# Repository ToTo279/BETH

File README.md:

# BETH - Badminton Equipment for Training and Health

## Projektbeschreibung
Das Elektronikprojekt konzentriert sich auf verschiedene Aspekte der Elektrotechnik, darunter die Programmierung von Mikrocontrollern, die Analyse und Umsetzung der Energieversorgung kleinerer Geräte sowie die Implementierung von Sensoren, optischen und akustischen Bausteinen. Das Hauptziel besteht darin, ein System zu entwickeln, das sowohl im sportlichen Bereich als auch im Freizeitbereich Anwendung findet. BETH (Badminton Equipment for Training and Health) wurde entwickelt, um Spielern die Möglichkeit zu geben, ihre Reaktionsfähigkeit, Bewegungskoordination und Ausdauer zu verbessern, indem es eine dynamische und unterhaltsame Umgebung schafft.

## Funktionen und Technologien
- Programmierung von ESP32 Mikrocontrollern und eines Raspberry Pi's
- Analyse des Energiekonsums und Umsetzung der Energieversorgung kleinerer Geräte
- Integration von Sensoren, Licht- und Tonbausteinen für innovative und interaktive Systeme

---

### Gehäuse
Das BETH-System besteht aus einer Basisstation und vier Satelliten. Die Basisstation, bestehend aus einem Raspberry Pi und einem Touchdisplay, verwendet ein käuflich erhältliches Gehäuse für optimale Bedienung und Sichtbarkeit.

Für die Satelliten wurde ein Gehäuse mittels 3D-Druck und CAD-Programm entworfen. Tough PLA für Unterteil und Brücke sowie CPE+ für Oberteil und Status-LED-Fenster sorgen für Robustheit und Flexibilität.

Das Unterteil des Gehäuses verfügt über Öffnungen für Lautsprecher, Taster, USB-C-Buchse und Status-LED. Auflageflächen für Spannungsversorgungs- und LED-Platinen sind integriert. M3-Schmelzgewinde gewährleisten eine sichere Schraubverbindung.

Die Brücke zwischen den Platinen ermöglicht eine modulare Montage. Das Oberteil beinhaltet einen LED-Streifen, einen Touchsensor und drei Abstandssensoren. Die glatte Oberfläche gewährleistet eine angenehme Haptik.

**Modelle für Gehäuse und Platinen befinden sich im Ordner "Modelle".**

### Energieversorgung

Dieser Abschnitt bietet einen Überblick über das Energiemodul des BETH-Projekts, einschließlich seiner Integration, Funktionsweise, verwendeten Komponenten, Schaltplan und Leiterplatte, sowie Tests und Reflexionen.

#### Eingliederung in das Projekt

Die Entscheidung für die Energieversorgung der Satelliten basierte auf der Wahl zwischen Netzbetrieb, Batterie oder Akkubetrieb. Die Akkubetriebsoption wurde gewählt, um Flexibilität, einfache Handhabung und ästhetisches Design zu gewährleisten. Das Energiemodul ist ein Schlüsselelement der Satelliten, neben dem ESP32 Mikrocontroller.

#### Funktionsweise

Das Energiemodul erfüllt verschiedene Anforderungen, darunter eine 45- bis 60-minütige Energieversorgung, Aufladung über einen USB-C-Anschluss, Bereitstellung von 5 Volt DC bei maximal 1,5 Ampere, Ein- und Ausschalten am Gehäuse, softwaregesteuertes Ausschalten und Schutz vor Gefahren.

#### Verwendete Baugruppen

- Batteriezelle (XTAR 18650)
- Charge IC (BQ24092DGQR)
- Step-up DC-DC Converter (TPS61085)
- eFuse (TPS259621DDAT)
- Ein-Aus-Schalter (CMOS J-K Flip Flop)
- Protection IC (XB8089D)

#### Schaltplan und Leiterplatte

Der Schaltplan und die Leiterplatte wurden unter Berücksichtigung der Datenblätter der Komponenten entwickelt. Der Schaltplan enthält ICs, passiven Bauteilen und Testpunkten. Die Leiterplatte wurde sorgfältig gestaltet, wobei auf großräumige Flächen an energiereichen Stellen und Testpunkte für einfaches Debugging geachtet wurde.

### Audio
#### Eingliederung in das Projekt
Die Umsetzung einer effektiven Audiowiedergabe erfordert präzise Signalverarbeitung und Kontrolle. Im Fokus steht die Audiowiedergabe, bei der mehrere Schaltungselemente kombiniert wurden, um optimale Klangqualität und Steuerbarkeit zu gewährleisten. Die Grundlage bildet ein Audioplayer-Modul, dem im Verlauf der Realisierung verschiedene Elemente hinzugefügt wurden.

##### Funktionsweise
1. **DF Player**
   - Ein DF Player bzw. ein Audioplayer-Modul von DFRobot wird verwendet.
   - Speziell für die Wiedergabe von Audiodateien mit einem einfachen Steuerungsprotokoll konzipiert.
   - Unterstützt Funktionen wie Abspielen, Pausieren, Stoppen, Vor- und Zurückspulen von Audiotracks.
   - Über eine serielle Schnittstelle (UART) vom Mikrocontroller (ESP32S) gesteuert.

2. **Addierer und Rekonstruktionsfilter**
   - Verwendung einer Schaltung mit einem Operationsverstärker (OPV), um rechte und linke Stereosignale zu kombinieren.
   - Ein Rekonstruktions-Tiefpassfilter minimiert Aliasing-Effekte und glättet das digitale Signal.

3. **Audio Verstärker**
   - Der LM386 Audioverstärkerchip ermöglicht eine effektive Verstärkung von Audiosignalen.
   - Die Schaltung umfasst verschiedene Bauteile, die in ihrer Kombination eine qualitativ hochwertige Audiowiedergabe gewährleisten.

4. **DC/DC Wandler**
   - Ein DC/DC-Wandler wird eingesetzt, um die Batteriespannung von +5V auf +12V umzuwandeln.
   - Ein Filterkondensator minimiert Eingangs- und Ausgangswelligkeit.
   - Eine Elektromagnetische Verträglichkeit (EMC) Schaltung gewährleistet störungsfreies Arbeiten in elektromagnetisch sensiblen Umgebungen.

##### Anleitung zur Nutzung
1. Lade Audiofiles auf die micro SD-Karte.
2. Verbinde die serielle Schnittstelle des DF Players mit der Steuerungseinheit.
3. Steuere die Audiowiedergabe über UART-Befehle.

##### Hinweise
- Beachte die Platzbeschränkungen bei der Implementierung der Audiofunktionen.
- Stelle sicher, dass die Spannungsversorgung und EMC-Richtlinien eingehalten werden.

### LED-Beleuchtung
#### Eingliederung in das Projekt
Die Integration der LED-Beleuchtung in das Projekt bietet eine ästhetische Komponente und erweitert die Funktionalität. Die Wahl der RGB-LEDs WS2812B ermöglicht die flexible Ansteuerung jeder einzelnen LED, was eine vielfältige Gestaltung der Beleuchtung und die Umsetzung verschiedener Spielmodi ermöglicht. Die LEDs dienen auch zur Anzeige von Statusinformationen wie dem Verbindungsstatus und dem Batteriezustand.

#### Funktionsweise
Die Platine für die LED-Beleuchtung wurde so gestaltet, dass sie neben den RGB-LEDs WS2812B auch alle notwendigen Komponenten enthält, um eine nahtlose Integration in das Gesamtsystem zu gewährleisten. Die Anordnung der LEDs in einem Ring und dem LED-Streifen ermöglichen die Erzeugung kreativer Lichteffekte, die das Spielerlebnis intensivieren.

Die WS2812B RGB-LEDs haben vier Pins: Versorgungsspannung, Masse, Eingangssignal und Ausgangssignal. Die Verbindung zwischen den LEDs erfolgt durch Verknüpfung des Ausgangssignal-Pins einer LED mit dem Eingangssignal-Pin der nächsten LED. Die Status-LED auf der Seite des Gehäuses kommuniziert über verschiedene Farben und Blinkmuster wichtige Informationen, wie den Verbindungsstatus mit anderen Satelliten oder den Batteriezustand.

#### Schaltplan
Es wurden 16 LEDs auf einer eigenen Platine kreisförmig angeordnet. Die LEDs sind mit dem Mikrocontroller verbunden, um das Eingangssignal, die Spannungsversorgung und die Masse zu erhalten, und leiten das Signal an die Status-LED und den LED-Streifen weiter.

#### PCB
Die Leiterplatte (PCB) wurde entsprechend dem Schaltplan erstellt. Die LEDs wurden in einem Kreis angeordnet, und auf der anderen Seite der Platine wurden der große Kondensator und der Widerstand platziert.

#### Programmierung
Für die Steuerung der LEDs wurde die Neopixel-Bibliothek von Adafruit Industries verwendet. Die Programmierung ermöglicht eine flexible und anpassbare visuelle Gestaltung, um das LEDmintons-Erlebnis zu verbessern. Die Integration dieser Programmierfunktionalitäten erlaubt die Steuerung der Beleuchtungseffekte in Echtzeit während des Spielbetriebs.

### Sensorik
#### Eingliederung in das Projekt
Im Sensorik-Kapitel wird die Integration der im Projekt verwendeten Sensoren beschrieben. Sensoren sind in der Lage, Informationen von der Umgebung aufzunehmen und elektrische Signale zu erzeugen. Im Projekt wurden Sensoren ausgewählt, die spezifische Anforderungen erfüllen sollten, darunter die Detektion des Badmintonschlägers auf unterschiedlichen Distanzen und die schnelle Reaktion auf Bewegungen.

#### Anforderungen
Die Auswahl der Sensoren erfolgte unter Berücksichtigung von Anforderungen wie der Reaktionsgeschwindigkeit und der Fähigkeit, Bewegungen auf kurze und lange Distanzen zu detektieren. Es wurden TOF-Sensoren (Time of Flight) ausgewählt, um die Entfernungen zuverlässig zu messen, sowie der eingebaute Touchsensor des ESP32 für die Detektion von Berührungen.

#### Funktionsweise
**TOF Sensoren**
Die Entfernungsmessung wird von TOF-Sensoren übernommen. Diese Sensoren wurden aufgrund ihrer Zuverlässigkeit, schnellen Reaktion und geringen Größe ausgewählt. Sie sind in der Lage, Entfernungen von 40 mm bis 4 m mit einer Genauigkeit von ±5 % zu messen. Die Messung basiert auf der Laufzeitmessung von Licht, das zum Zielobjekt geschossen wird und reflektiert zurückkehrt.

**Touch Sensor**
Der Touchsensor basiert auf den Touchpins des ESP32. Die Berührung einer Metallplatte, die mit einem Pin verbunden ist, sendet ein elektrisches Signal an den ESP32. Schutzmaßnahmen, wie eine Supressordiode und ein Widerstand, wurden implementiert, um Überladungen zu verhindern.

**Programmierung und Interrupts**
Um eine schnelle Reaktion der TOF-Sensoren zu gewährleisten, wurden Interrupts in der Programmierung verwendet. Diese ermöglichen eine zuverlässige Detektion von Umweltveränderungen und eine unmittelbare Weiterleitung an den ESP32.

### Kommunikation
#### Eingliederung in das Projekt
Dieser Abschnitt beschäftigt sich mit der technischen Implementierung und Realisierung der Kommunikation zwischen den Satelliten (ESP32) und der Basisstation (Raspberry Pi). Die Kommunikation spielt eine entscheidende Rolle, da sämtliche Benutzerinteraktionen über die Basisstation erfolgen.

#### Kommunikationsmethoden
Zur Gestaltung des Projekts wurden zwei Kommunikationsmethoden in Betracht gezogen: Bluetooth und drahtlose Verbindung (WLAN). Nach sorgfältiger Überlegung wurde WLAN als die bessere Option gewählt, da es die spezifizierten Anforderungen besser erfüllt. Als Kommunikationsprotokoll wurde TCP (Transmission Control Protocol) ausgewählt, um eine stabile und zuverlässige Verbindung zu ermöglichen.

#### Anforderungen
Die formulierten Anforderungen umfassen unter anderem die gleichzeitige Verbindung aller Satelliten mit der Basisstation, eine stabile Verbindung, schnelle Erkennung von Unterbrechungen, minimaler Paketverlust, automatische Wiederherstellung der Verbindung nach Unterbrechungen und unabhängige Verbindungen zwischen der Basisstation und den Satelliten.

#### Implementierung
Die Kommunikation erfolgt über WLAN unter Verwendung von TCP. Die Basisstation (Raspberry Pi) erstellt einen drahtlosen Hotspot, und die Satelliten (ESP32) stellen eine TCP-Verbindung her. Die Kommunikation erfolgt in JSON-Format für die Übertragung von Nachrichten.

##### Raspberry Pi Programmierung
Die Basisstations-Software wurde in Python (Version 3.12) implementiert. Sie erstellt einen kabellosen Hotspot, verwaltet die Kommunikation und bietet eine grafische Benutzeroberfläche (GUI) für Benutzerinteraktionen.

##### ESP-32 Programmierung
Die Satelliten-Software wurde in C++ mit Hilfe von Espressifs Wifi-Bibliothek und ArduinoJson implementiert. Die Satelliten senden regelmäßig Nachrichten, die die Satellite-ID und den Batteriestand enthalten.

##### Test der Kommunikation
Verschiedene Testfälle wurden durchgeführt, darunter der reibungslose Betrieb paralleler Verbindungen und die erfolgreiche Erkennung von Verbindungsunterbrechungen. Die Kommunikation wurde über mehrere Stunden ohne Unterbrechungen getestet.

---

## Installation und Nutzung
1. Klone das Repository: `git@github.com:ToTo279/BETH.git`
2. Folge den Anweisungen in der Installationsanleitung, um das System einzurichten.
3. Erkunde die verschiedenen Funktionen und Anwendungsbereiche im Projekt.

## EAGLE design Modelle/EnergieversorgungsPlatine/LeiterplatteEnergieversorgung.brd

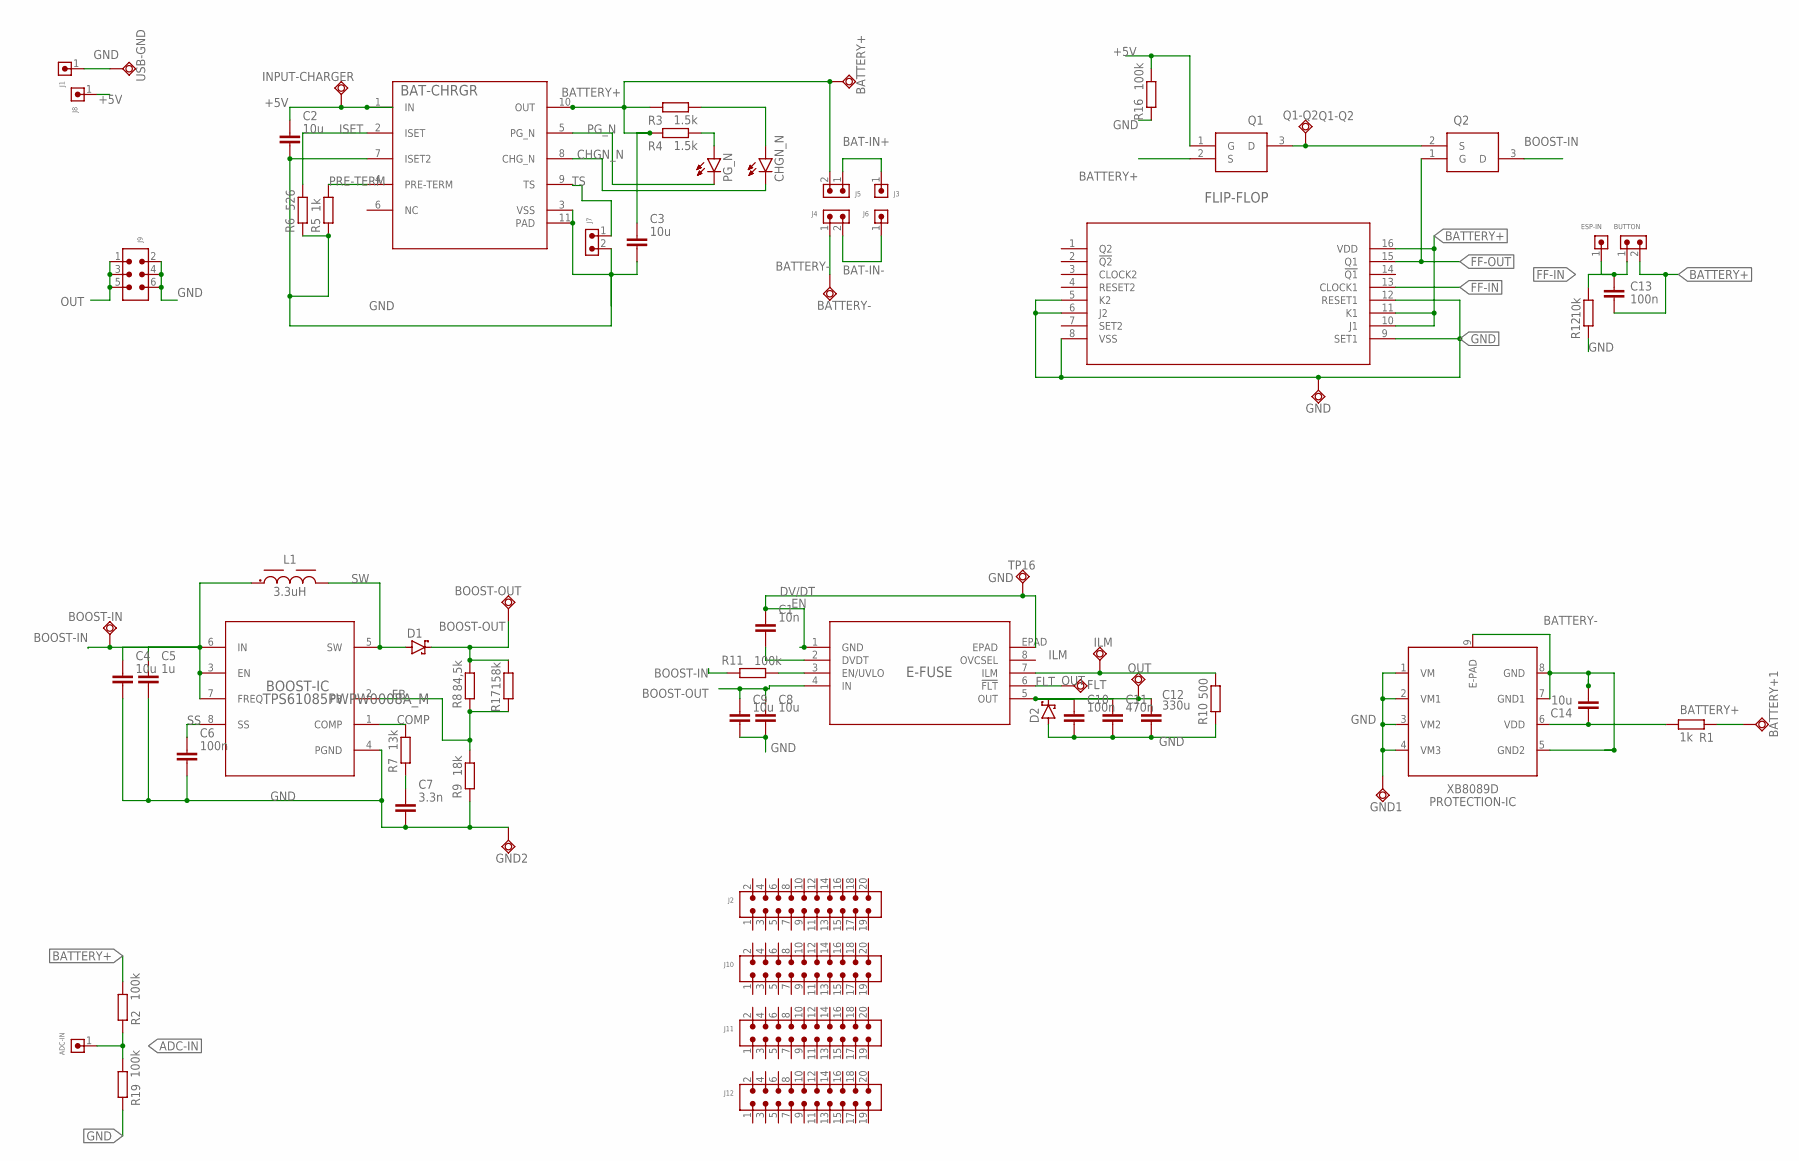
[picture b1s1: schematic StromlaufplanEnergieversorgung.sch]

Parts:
ADC-IN: 6130XX11121_61300111121; 61300111121
BAT-CHRGR: BQ24092DGQRDGQ0010D_NV_L; DGQ0010D_NV_L
BATTERY+, BATTERY+1: TPSQPAD1-13; P1-13
BATTERY-: TPSQPAD1-13; P1-13
BOOST-IC: TPS61085PWPW0008A_M; PW0008A_M
BOOST-IN: TPSQPAD1-13; P1-13
BOOST-OUT: TPSQPAD1-13; P1-13
BUTTON: 6130XX11121_61300211121; 61300211121
C1: 10n; CAPC3216X135
C2, C3, C4, C8, C9, C14: 10u; CAPC3216X135
C5: 1u; CAPC3216X135
C6, C10, C13: 100n; CAPC3216X135
C7: 3.3n; CAPC3216X135
C11: 470n; CAPC3216X135
C12: 330u; CAPRD550W60D1025H1250B
CHGN_N: LEDCHIPLED_1206; CHIPLED_1206
D1, D2: SCHOTTKY-DIODESMD; SMB
E-FUSE: TPS259620DDARSOIC_20DDAR_TEX-M; SOIC_20DDAR_TEX-M
ESP-IN: 6130XX11121_61300111121; 61300111121
FLIP-FLOP: CD4027BNSRNS16; NS16
FLT: TPSQPAD1-13; P1-13
GND, GND1, GND2: TPSQPAD1-13; P1-13
ILM: TPSQPAD1-13; P1-13
INPUT-CHARGER: TPSQPAD1-13; P1-13
J1, J3, J6, J8: 6130XX11121_61300111121; 61300111121
J2, J10, J11, J12: 6130XX21121_61302021121; 61302021121
J4, J5, J7: 6130XX11121_61300211121; 61300211121
J9: 6130XX21121_61300621121; 61300621121
L1: 3.3uH; WE-PD_7345
OUT: TPSQPAD1-13; P1-13
PG_N: LEDCHIPLED_1206; CHIPLED_1206
PROTECTION-IC: XB8089D
Q1, Q2: DMP3098L-7; SOT96P240X110-3N
Q1-Q2: TPSQPAD1-13; P1-13
R1, R5: 1k; RESC3216X70
R2, R11, R16, R19: 100k; RESC3216X70
R3, R4: 1.5k; RESC3216X70
R6: 526; RESC3216X70
R7: 13k; RESC3216X70
R8: 84,5k; RESC3216X70
R9: 18k; RESC3216X70
R10: 500; RESC3216X70
R12: 10k; RESC3216X70
R17: 158k; RESC3216X70
TP16: TPSQPAD1-13; P1-13
USB-GND: TPSQPAD1-13; P1-13

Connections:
+5V: BAT-CHRGR.1 (IN), C2.1, INPUT-CHARGER.TP, J8.1, Q1.1 (G), R16.2
ADC-IN: ADC-IN.1, R2.2, R19.1
BAT-IN+: J3.1, J5.1
BAT-IN-: J4.2, J6.1
BATTERY+: BAT-CHRGR.10 (OUT), BATTERY+.TP, BATTERY+1.TP, BUTTON.2, C3.1, C13.2, FLIP-FLOP.10 (J1), FLIP-FLOP.11 (K1), FLIP-FLOP.16 (VDD), J5.2, Q1.2 (S), R1.1, R2.1, R3.2, R4.2
BATTERY-: BATTERY-.TP, C14.2, J4.1, PROTECTION-IC.5 (GND2), PROTECTION-IC.7 (GND1), PROTECTION-IC.8 (GND), PROTECTION-IC.9 (E-PAD)
BOOST-IN: BOOST-IC.3 (EN), BOOST-IC.6 (IN), BOOST-IC.7 (FREQ), BOOST-IN.TP, C4.1, C5.1, L1.1, Q2.3 (D), R11.1
BOOST-OUT: BOOST-OUT.TP, C8.1, C9.1, D1.C, E-FUSE.4 (IN), R8.2, R17.2
CHGN_N: BAT-CHRGR.8 (CHG_N), CHGN_N.C
COMP: BOOST-IC.1 (COMP), R7.2
DV/DT: C1.2, E-FUSE.2 (DVDT)
EN: E-FUSE.3 (EN/UVLO), R11.2
FB: BOOST-IC.2 (FB), R8.1, R9.2, R17.1
FF-IN: BUTTON.1, C13.1, ESP-IN.1, FLIP-FLOP.13 (CLOCK1), R12.2
FF-OUT: FLIP-FLOP.15 (Q1), Q2.1 (G)
FLT: E-FUSE.6 (!FLT), FLT.TP
GND: BAT-CHRGR.3 (VSS), BAT-CHRGR.7 (ISET2), BAT-CHRGR.11 (PAD), BOOST-IC.4 (PGND), C1.1, C2.2, C3.2, C4.2, C5.2, C6.2, C7.2, C8.2, C9.2, C10.2, C11.2, C12.2, D2.A, E-FUSE.1 (GND), E-FUSE.EPAD, FLIP-FLOP.5 (K2), FLIP-FLOP.6 (J2), FLIP-FLOP.8 (VSS), FLIP-FLOP.9 (SET1), FLIP-FLOP.12 (RESET1), GND.TP, GND1.TP, GND2.TP, J1.1, J7.2, J9.2, J9.4, J9.6, PROTECTION-IC.1 (VM), PROTECTION-IC.2 (VM1), PROTECTION-IC.3 (VM2), PROTECTION-IC.4 (VM3), R5.1, R6.1, R9.1, R10.1, R12.1, R16.1, R19.2, TP16.TP, USB-GND.TP
ILM: E-FUSE.7 (ILM), ILM.TP, R10.2
ISET: BAT-CHRGR.2 (ISET), R6.2
unnamed: C14.1, PROTECTION-IC.6 (VDD), R1.2
unnamed: CHGN_N.A, R3.1
unnamed: PG_N.A, R4.1
unnamed: C7.1, R7.1
OUT: C10.1, C11.1, C12.1, D2.C, E-FUSE.5 (OUT), J9.1, J9.3, J9.5, OUT.TP
PG_N: BAT-CHRGR.5 (PG_N), PG_N.C
PRE-TERM: BAT-CHRGR.4 (PRE-TERM), R5.2
Q1-Q2: Q1.3 (D), Q1-Q2.TP, Q2.2 (S)
SS: BOOST-IC.8 (SS), C6.1
SW: BOOST-IC.5 (SW), D1.A, L1.2
TS: BAT-CHRGR.9 (TS), J7.1

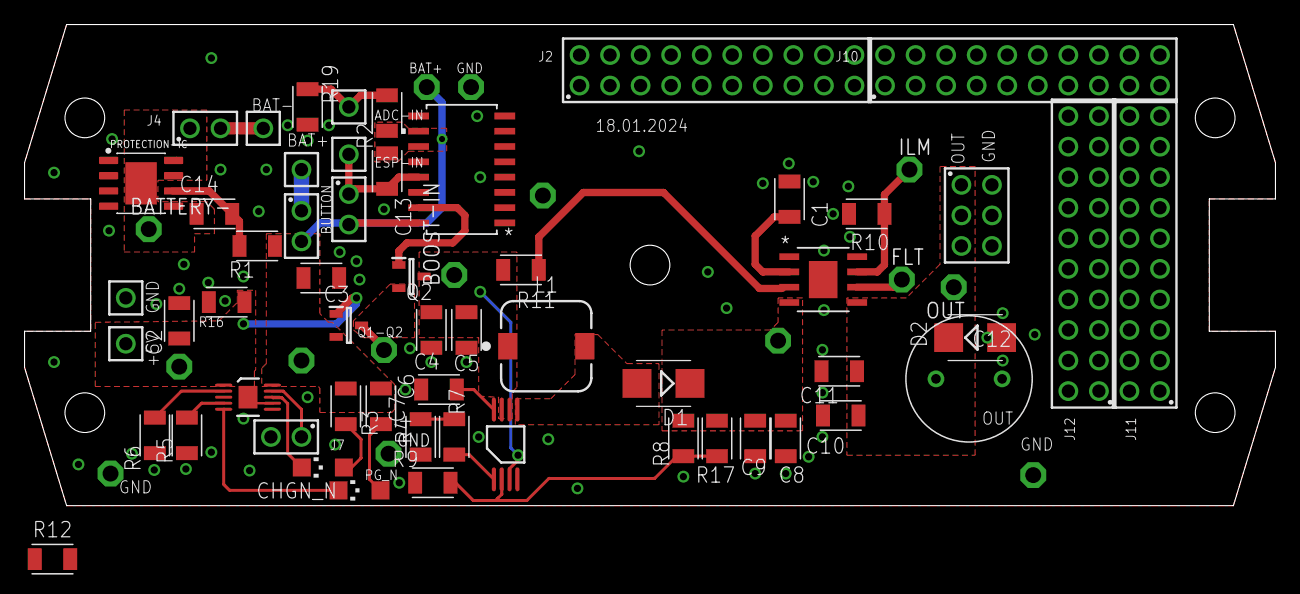
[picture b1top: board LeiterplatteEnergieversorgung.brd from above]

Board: 2 copper layers, 104.0 x 40.0 mm, 71 parts (0 on the bottom side), 30 nets.

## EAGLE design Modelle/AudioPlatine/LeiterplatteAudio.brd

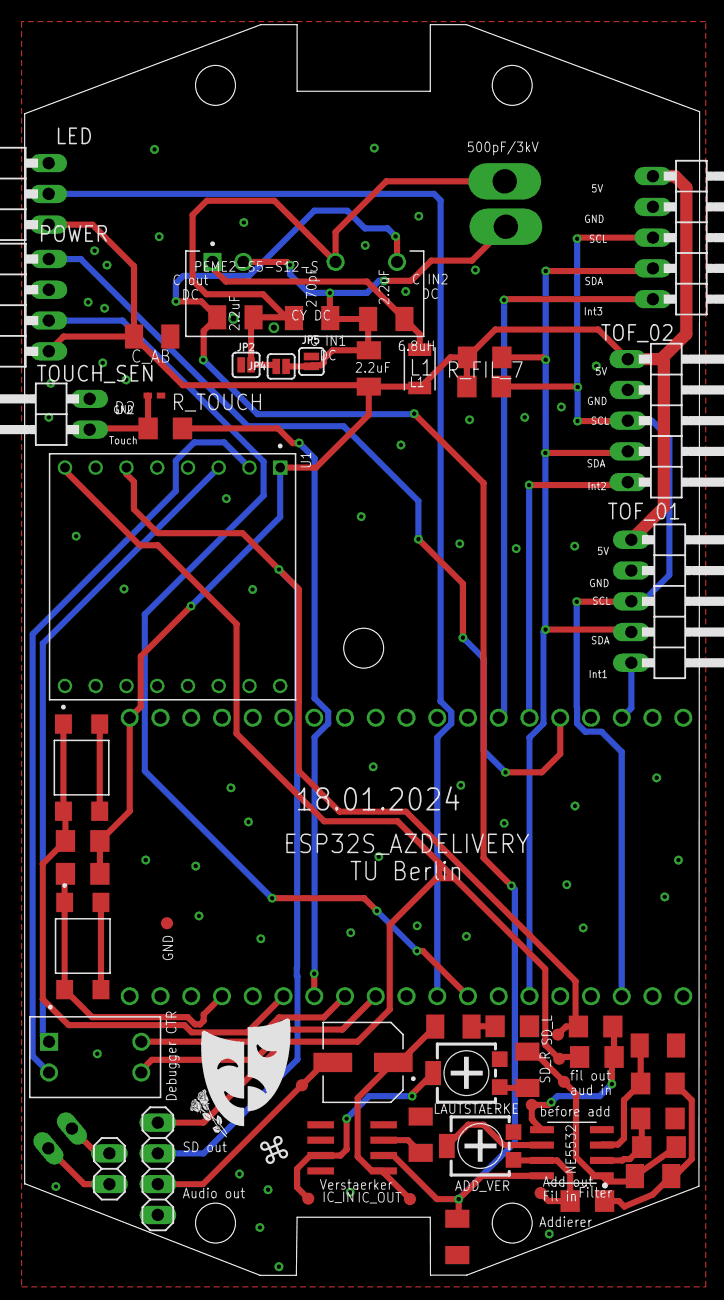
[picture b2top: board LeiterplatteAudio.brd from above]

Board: 2 copper layers, 55.7 x 103.3 mm, 59 parts (1 on the bottom side), 39 nets.

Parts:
ADD_OUT->FIL_IN: PTR1TP10R; TP10R
ADD_VER: 2k; RTRIM4G/J
AUDIO_OUT1: PTR1TP10R; TP10R
C1: 220uF; CAP_EEEFTE221XAP
C2: 47n; C1206K
C2_BYPASS: C1206K
CY_DC: 270pF/3kV; C1206K
C_AB: 100nF; C1206K
C_COUPLING: 680pf; C1206K
C_FIL_1, C_FIL_2: 680pf; C1206K
C_IN01_DC, C_IN02_DC: 2.2uF/25V; C1206K
C_OUT_DC: 2.2uF/25V; C1206K
D2: 1PS79SB30; SOD523
FIL_OUT->AUDIO_IN: PTR1TP10R; TP10R
GND: PTR1TP10R; TP10R
IC1: LM386M-1; SO08
IC2: NE5532_SOIC; SOIC127P600X175-8N
IC_IN: PTR1TP10R; TP10R
IC_OUT: PTR1TP10R; TP10R
JP1, JP6: PINHD-1X2; 1X02
JP2, JP4, JP5: JUMPER-SMT_2_NO_SILK; SMT-JUMPER_2_NO_SILK
JP3: PINHD-1X4; 1X04
L1: 6.8 μH; INDC3216X190
LAUTSTAERKE: RTRIM4G/J
LED: PINHD-1X3/90; 1X03/90
POWER: PINHD-1X4/90; 1X04/90
PS1: PEME2-S5-S12-S; CONV_PEME2-S5-S12-S
R2: 10; R1206
R_ADD_L: 1k; R1206
R_ADD_R: 1k; R1206
R_FIL_1: 13k; R1206
R_FIL_2: 43k; R1206
R_FIL_3: 56k; R1206
R_FIL_4: 33k; R1206
R_FIL_6, R_FIL_7: 100; R1206
R_TAST_1, R_TAST_2: 1k; R1206
R_TOUCH: 100; R1206
S1: DS02-254-2L-02BE; SW_DS02-254-2L-02BE
S2, S3: TL3305AF160QG; SW_TL3305AF160QG
SD_L: PTR1TP10R; TP10R
SD_R: PTR1TP10R; TP10R
TOF_01, TOF_02, TOF_03: PINHD-1X5/90; 1X05/90
TOUCH_SEN: PINHD-1X2/90; 1X02/90
TP1, TP2: TPSQPAD1-20Y; P1-20Y
U1: DFR0299; MODULE_DFR0299
U$1: ESP32S_AZDELIVERY
VER_KON.: 47n; C1206K
VOR_ADD: PTR1TP10R; TP10R

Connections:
+12V: C_OUT_DC.1, IC1.6, IC2.8, PS1.7, VER_KON..2
ADC-IN: POWER.4, U$1.GPIO34
AUDIO_OUT: AUDIO_OUT1.TP, C1.2, JP3.2
AUTO-OUT: POWER.2, U$1.GPIO19
FIL_IN: ADD_OUT->FIL_IN.TP, ADD_VER.1, IC2.7, R_FIL_1.2
FIL_OUT: C_COUPLING.2, C_FIL_1.2, FIL_OUT->AUDIO_IN.TP, IC2.1, R_FIL_4.2
GND: ADD_VER.3, C2_BYPASS.1, C_AB.1, C_FIL_2.1, D2.2, GND.TP, IC1.2, IC1.4, IC2.4, JP2.2, JP3.1, JP5.1, LAUTSTAERKE.3, LED.3, POWER.3, R2.1, R_FIL_3.1, S2.3, S2.4, S3.3, S3.4, TOF_01.2, TOF_02.2, TOF_03.2, TOUCH_SEN.2, U1.7, U1.10, U$1.GND1, U$1.GND2, U$1.GND3, VER_KON..1
IC_IN: IC1.3, IC_IN.TP, LAUTSTAERKE.2
IC_OUT: C1.1, C2.2, IC1.5, IC_OUT.TP
INTERRUPT01: TOF_01.5, U$1.GPIO36
INTERRUPT02: TOF_02.5, U$1.GPIO35
INTERRUPT03: TOF_03.5, U$1.GPIO32
LED_SIG: LED.2, U$1.GPIO18
unnamed: IC2.2, R_FIL_3.2, R_FIL_4.1
unnamed: C2_BYPASS.2, IC1.7
unnamed: C2.1, R2.2
unnamed: C_FIL_1.1, R_FIL_1.1, R_FIL_2.2
unnamed: C_FIL_2.2, IC2.3, R_FIL_2.1
unnamed: S1.1A, U1.3
unnamed: S1.2A, U1.2
unnamed: JP1.2, JP6.2
unnamed: JP1.1, JP6.1
unnamed: D2.1, R_TOUCH.1, TOUCH_SEN.1
unnamed: ADD_VER.2, IC2.6
unnamed: C_IN02_DC.2, L1.2, PS1.1
unnamed: CY_DC.2, C_OUT_DC.2, JP2.1, JP4.1, PS1.5, TP2.TP
unnamed: CY_DC.1, C_IN01_DC.1, C_IN02_DC.1, JP4.2, JP5.2, PS1.2, TP1.TP
RX: S1.2B, U$1.GPIO17
SCL: R_FIL_6.2, TOF_01.3, TOF_02.3, TOF_03.3, U$1.GPIO22
SDA: R_FIL_7.2, TOF_01.4, TOF_02.4, TOF_03.4, U$1.GPIO21
SD_L: JP3.3, R_ADD_L.1, SD_L.TP, U1.6
SD_R: JP3.4, R_ADD_R.1, SD_R.TP, U1.8
TAST_1: R_TAST_1.1, S2.1, S2.2, U$1.GPIO0
TAST_2: R_TAST_2.1, S3.1, S3.2, U$1.GPIO15
TOUCH_SIG: R_TOUCH.2, U$1.GPIO4
TX: S1.1B, U$1.GPIO16
VCC: C_AB.2, C_IN01_DC.2, L1.1, LED.1, POWER.1, R_FIL_6.1, R_FIL_7.1, R_TAST_1.2, R_TAST_2.2, TOF_01.1, TOF_02.1, TOF_03.1, U1.1, U$1.+5V
VER_IN: C_COUPLING.1, LAUTSTAERKE.1
VOR_ADD: IC2.5, R_ADD_L.2, R_ADD_R.2, VOR_ADD.TP

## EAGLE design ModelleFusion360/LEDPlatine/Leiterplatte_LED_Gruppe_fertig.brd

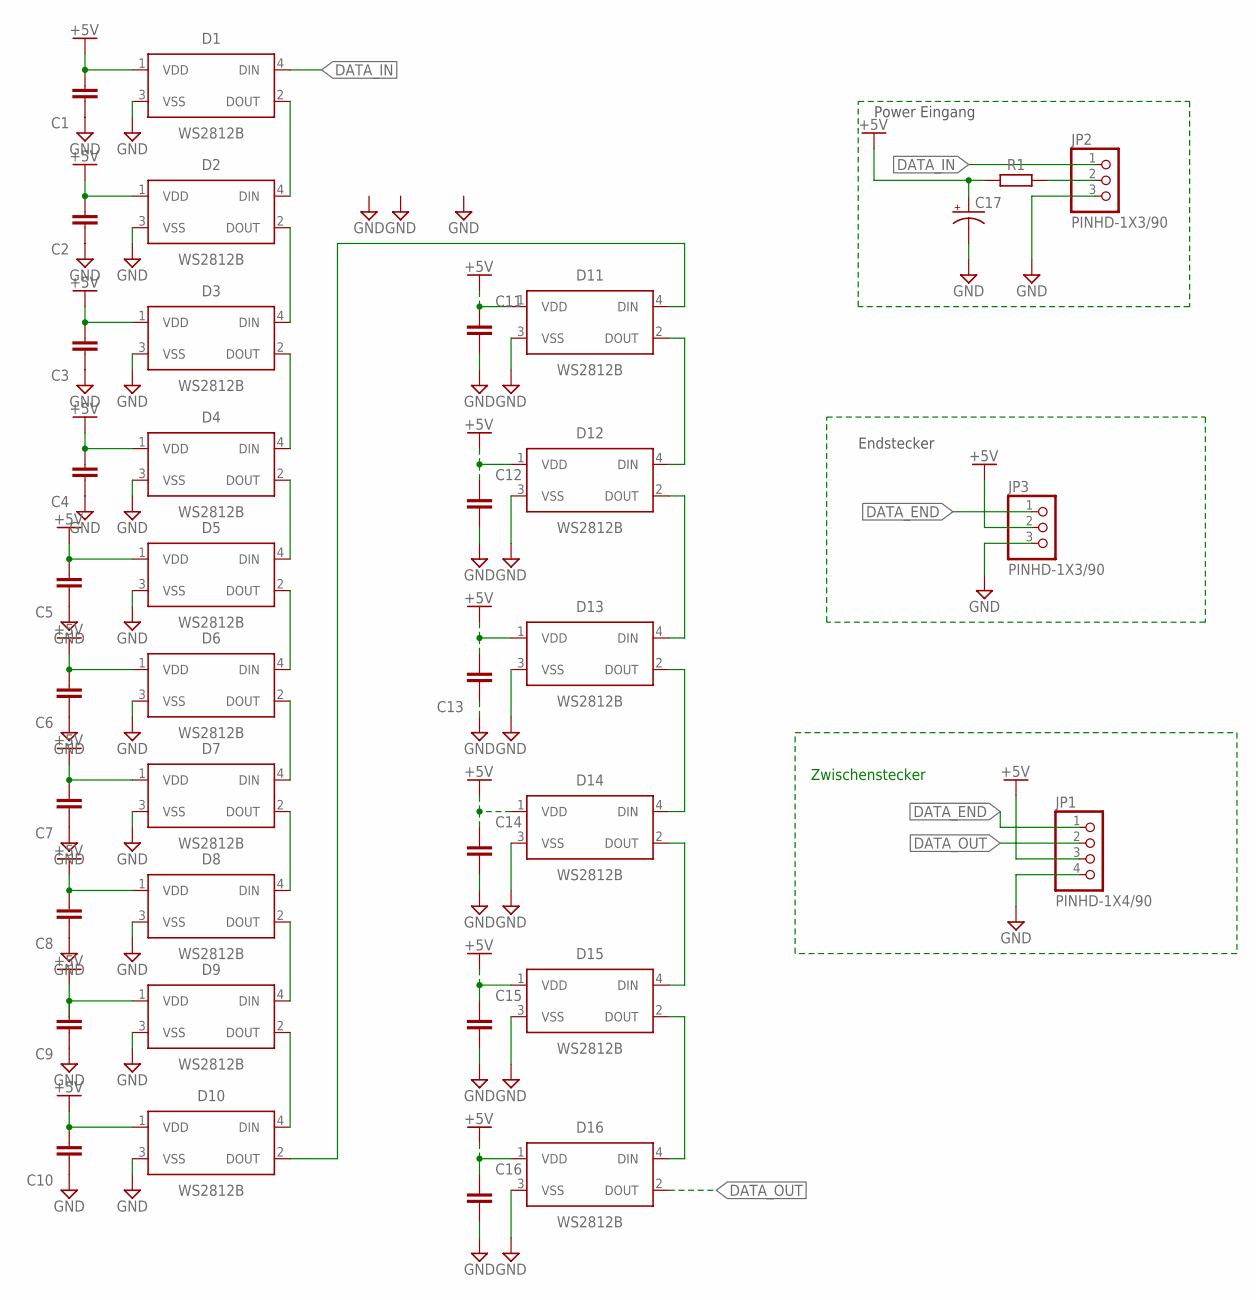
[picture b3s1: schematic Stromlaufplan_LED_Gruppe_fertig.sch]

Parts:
C1, C2, C3, C4, C5, C6, C7, C8, C9, C10, C11, C12, C13, C14, C15, C16: C_CHIP-1206(3216-METRIC); CAPC3216X135
C17: C-POL-US_TANTALUM-1206(3216-METRIC); CAPMP3216X180N
D1, D2, D3, D4, D5, D6, D7, D8, D9, D10, D11, D12, D13, D14, D15, D16: WS2812B
JP1: PINHD-1X4/90; 1X04/90
JP2, JP3: PINHD-1X3/90; 1X03/90
R1: R_CHIP-1206(3216-METRIC); RESC3216X70

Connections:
+5V: C1.2, C2.2, C3.2, C4.2, C5.2, C6.2, C7.2, C8.2, C9.2, C10.2, C11.1, C12.1, C13.2, C14.1, C15.1, C16.1, C17.1 (+), D1.1 (VDD), D2.1 (VDD), D3.1 (VDD), D4.1 (VDD), D5.1 (VDD), D6.1 (VDD), D7.1 (VDD), D8.1 (VDD), D9.1 (VDD), D10.1 (VDD), D11.1 (VDD), D12.1 (VDD), D13.1 (VDD), D14.1 (VDD), D15.1 (VDD), D16.1 (VDD), JP1.3, JP3.2, R1.1
DATA_END: JP1.1, JP3.1
DATA_IN: D1.4 (DIN), JP2.1
DATA_OUT: D16.2 (DOUT), JP1.2
GND: C1.1, C2.1, C3.1, C4.1, C5.1, C6.1, C7.1, C8.1, C9.1, C10.1, C11.2, C12.2, C13.1, C14.2, C15.2, C16.2, C17.2 (-), D1.3 (VSS), D2.3 (VSS), D3.3 (VSS), D4.3 (VSS), D5.3 (VSS), D6.3 (VSS), D7.3 (VSS), D8.3 (VSS), D9.3 (VSS), D10.3 (VSS), D11.3 (VSS), D12.3 (VSS), D13.3 (VSS), D14.3 (VSS), D15.3 (VSS), D16.3 (VSS), JP1.4, JP2.3, JP3.3
unnamed: D14.2 (DOUT), D15.4 (DIN)
unnamed: D15.2 (DOUT), D16.4 (DIN)
unnamed: JP2.2, R1.2
unnamed: D2.2 (DOUT), D3.4 (DIN)
unnamed: D3.2 (DOUT), D4.4 (DIN)
unnamed: D4.2 (DOUT), D5.4 (DIN)
unnamed: D5.2 (DOUT), D6.4 (DIN)
unnamed: D6.2 (DOUT), D7.4 (DIN)
unnamed: D7.2 (DOUT), D8.4 (DIN)
unnamed: D8.2 (DOUT), D9.4 (DIN)
unnamed: D9.2 (DOUT), D10.4 (DIN)
unnamed: D10.2 (DOUT), D11.4 (DIN)
unnamed: D11.2 (DOUT), D12.4 (DIN)
unnamed: D12.2 (DOUT), D13.4 (DIN)
unnamed: D13.2 (DOUT), D14.4 (DIN)
unnamed: D1.2 (DOUT), D2.4 (DIN)

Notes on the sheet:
Power Eingang
Zwischenstecker
Endstecker

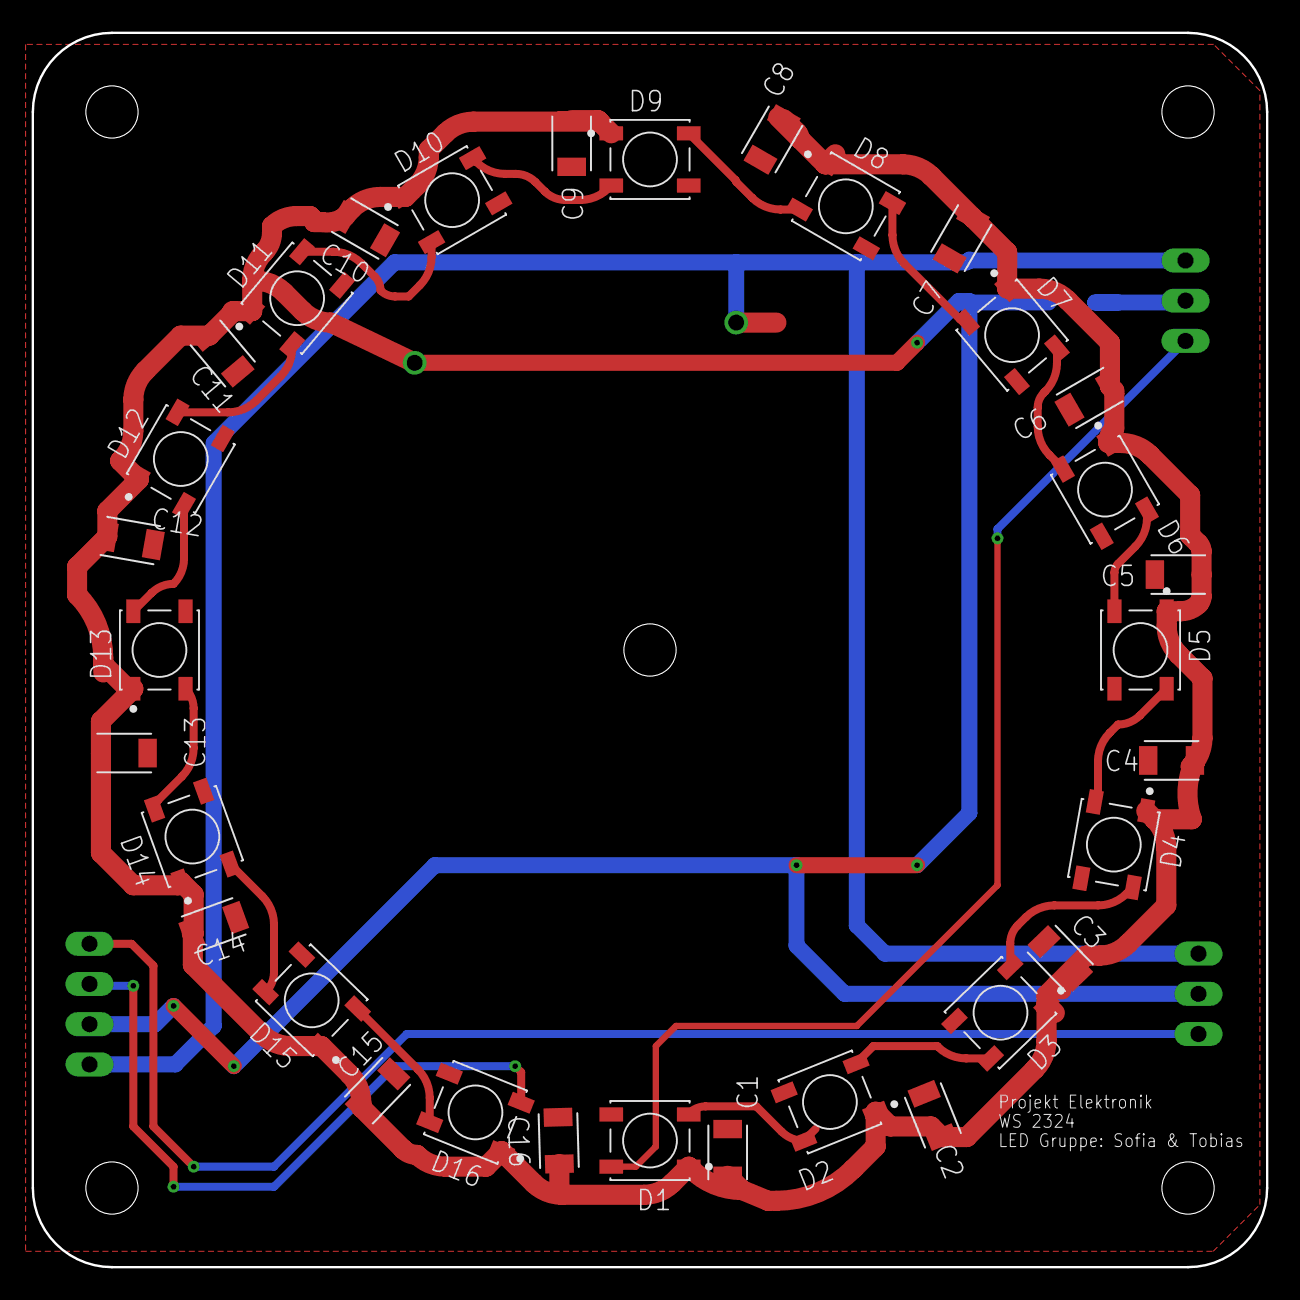
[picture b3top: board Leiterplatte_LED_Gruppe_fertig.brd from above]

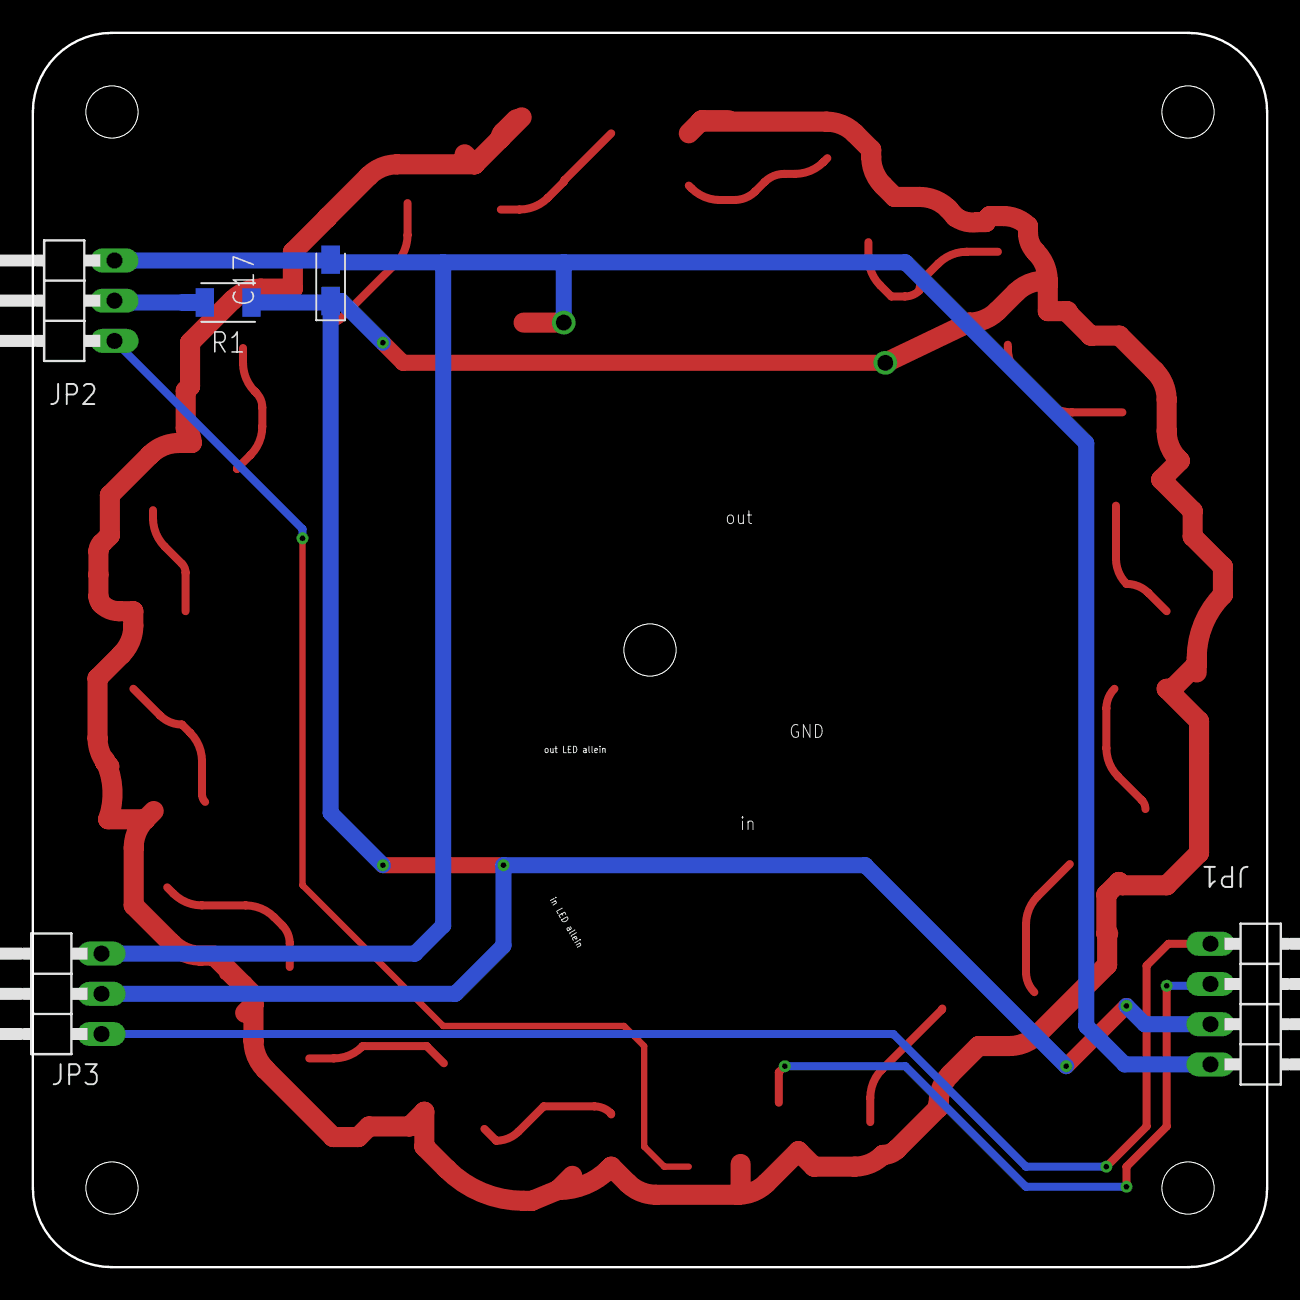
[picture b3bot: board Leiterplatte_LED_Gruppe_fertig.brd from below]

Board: 2 copper layers, 78.0 x 78.0 mm, 37 parts (5 on the bottom side), 21 nets.

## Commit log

2024-02-22 Adding code files to the project
2024-02-24 led modell added
2024-02-24 modelle added
2024-02-24 umbenannt
2024-02-24 gehäuse added
2024-02-24 code ordner angelegt

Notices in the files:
parts and their libraries:
SparkFun-Jumpers: Licensing: Creative Commons ShareAlike 4.0 International - https://creativecommons.org/licenses/by-sa/4.0
61001021121_Eagle_WR-PHD_rev19a: Copyright: Würth Elektronik
COPYRIGHT: Copyright (C) 2023 Ultra Librarian. All rights reserved.
